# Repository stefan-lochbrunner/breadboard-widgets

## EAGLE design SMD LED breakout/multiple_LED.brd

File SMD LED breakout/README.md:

# SMD LED breakout
------------------

Straight forward SMD LED breakout. To be used between the inside of a breadboard and its power rails. [more info](https://hackaday.io/project/6332-breadboard-widgets/log/27568-1-5x-smd-led-breakout)

#### Single

#### Multi

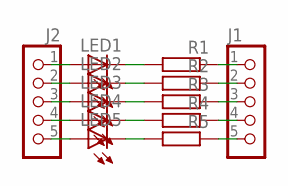
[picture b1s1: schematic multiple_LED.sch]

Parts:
J1, J2: CON_HEADER_1X05-PTH; M1X5
LED1, LED2, LED3, LED4, LED5: LED-0805; LED-805
R1, R2, R3, R4, R5: RESISTOR-0603; R603

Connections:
IN: J2.1, LED1.A
IN1: J2.2, LED2.A
IN2: J2.3, LED3.A
IN3: J2.4, LED4.A
IN4: J2.5, LED5.A
unnamed: LED2.C, R2.2
unnamed: LED1.C, R1.2
unnamed: LED3.C, R3.2
unnamed: LED4.C, R4.2
unnamed: LED5.C, R5.2
OUT: J1.1, R1.1
OUT1: J1.2, R2.1
OUT2: J1.3, R3.1
OUT3: J1.4, R4.1
OUT4: J1.5, R5.1

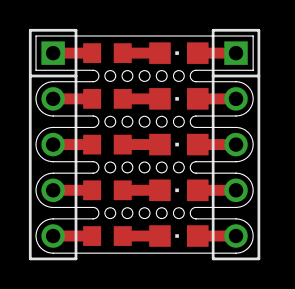
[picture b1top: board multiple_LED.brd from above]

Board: 2 copper layers, 12.1 x 12.1 mm, 12 parts (0 on the bottom side), 15 nets.

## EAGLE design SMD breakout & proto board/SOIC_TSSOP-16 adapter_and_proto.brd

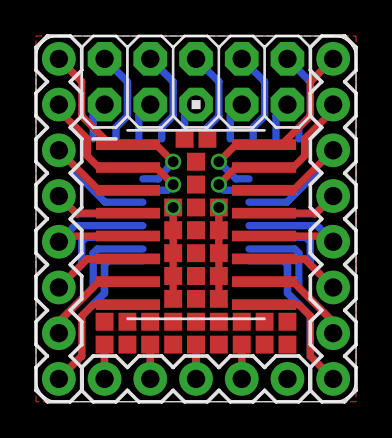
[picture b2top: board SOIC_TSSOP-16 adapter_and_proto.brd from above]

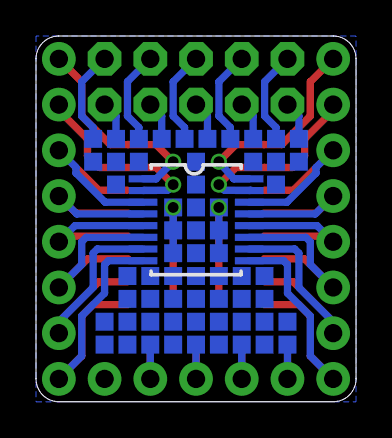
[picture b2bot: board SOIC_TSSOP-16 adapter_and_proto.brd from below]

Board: 2 copper layers, 17.8 x 20.3 mm, 104 parts (62 on the bottom side), 33 nets.

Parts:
JP1, JP2: 1X08_ROUND
JP3: AVR_ICSP
JP4: 1X05
SOIC-16: SOIC-16NW
TP1, TP2, TP3, TP4, TP5, TP6, TP7, TP8, TP9, TP10, TP11, TP12, TP13, TP14, TP15, TP16, TP17, TP18, TP19, TP20, TP21, TP22, TP23, TP24, TP25, TP26, TP27, TP28, TP29, TP30, TP31, TP32, TP33, TP34, TP35, TP36, TP37, TP38, TP39, TP40, TP41, TP42, TP43, TP44, TP45, TP46, TP47, TP48, TP49, TP50, TP51, TP52, TP53, TP54, TP55, TP56, TP57, TP58, TP59, TP60, TP61, TP62, TP63, TP64, TP65, TP66, TP67, TP68, TP69, TP70, TP71, TP72, TP73, TP74, TP75, TP76, TP77, TP78, TP79, TP80, TP81, TP82, TP83, TP84, TP85, TP86, TP87, TP88, TP89, TP90, TP91, TP92, TP93, TP94, TP95, TP96, TP97, TP98: TPSQTP10SQ; TP10SQ
TSSOP-16: TSSOP16

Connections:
1: JP1.8, SOIC-16.P1, TSSOP-16.16
2: JP1.7, SOIC-16.P2, TSSOP-16.15
3: JP1.6, SOIC-16.P3, TSSOP-16.14
4: JP1.5, SOIC-16.P4, TSSOP-16.13
5: JP1.4, SOIC-16.P5, TSSOP-16.12
6: JP1.3, SOIC-16.P6, TSSOP-16.11
7: JP1.2, SOIC-16.P7, TSSOP-16.10
8: JP1.1, SOIC-16.P8, TSSOP-16.9
9: JP2.8, SOIC-16.P9, TSSOP-16.8
10: JP2.7, SOIC-16.P10, TSSOP-16.7
11: JP2.6, SOIC-16.P11, TSSOP-16.6
12: JP2.5, SOIC-16.P12, TSSOP-16.5
13: JP2.4, SOIC-16.P13, TSSOP-16.4
14: JP2.3, SOIC-16.P14, TSSOP-16.3
15: JP2.2, SOIC-16.P15, TSSOP-16.2
16: JP2.1, SOIC-16.P16, TSSOP-16.1
D+: JP4.3, TP13.TP, TP17.TP
D-: JP4.2, TP14.TP, TP18.TP
GND: JP4.5, TP11.TP, TP20.TP
ID: JP4.4, TP12.TP, TP16.TP
unnamed: JP3.1, TP1.TP
unnamed: JP3.3, TP2.TP
unnamed: JP3.5, TP3.TP
unnamed: JP3.7, TP4.TP
unnamed: JP3.9, TP5.TP
unnamed: JP3.2, TP6.TP
unnamed: JP3.4, TP7.TP
unnamed: JP3.6, TP8.TP
unnamed: JP3.8, TP9.TP
unnamed: JP3.10, TP10.TP
RAIL1: TP25.TP, TP26.TP, TP27.TP, TP36.TP, TP37.TP, TP38.TP, TP39.TP, TP40.TP
RAIL2: TP28.TP, TP29.TP, TP30.TP, TP31.TP, TP32.TP, TP33.TP, TP34.TP, TP35.TP
VDD: JP4.1, TP15.TP, TP19.TP

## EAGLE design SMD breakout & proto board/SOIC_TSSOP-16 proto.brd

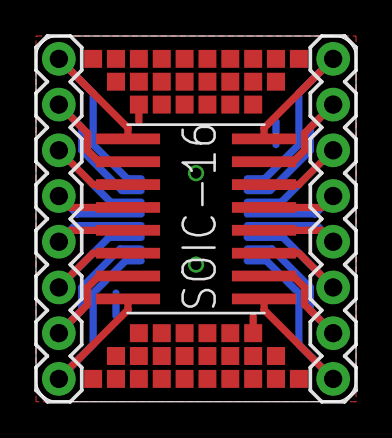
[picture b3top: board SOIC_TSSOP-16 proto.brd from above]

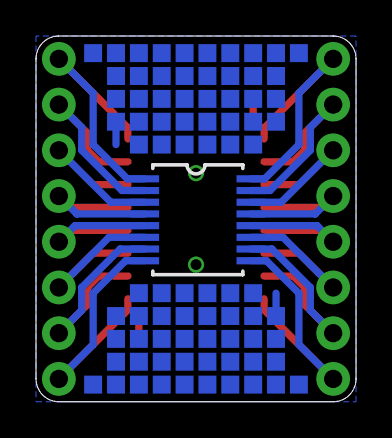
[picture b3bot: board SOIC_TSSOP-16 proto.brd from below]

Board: 2 copper layers, 17.8 x 20.3 mm, 132 parts (81 on the bottom side), 17 nets.

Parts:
E$1, E$2, E$3, E$4, E$5, E$6, E$7, E$8, E$9, E$10, E$11, E$12, E$13, E$14, E$15, E$16, E$17, E$18, E$19, E$20, E$21, E$22, E$23, E$24, E$25, E$26, E$27, E$28, E$29, E$30, E$31, E$32, E$33, E$34, E$35, E$36, E$37, E$38, E$39, E$40, E$41, E$42, E$43, E$44, E$45, E$46, E$47, E$48, E$49, E$50, E$51, E$52, E$53, E$54, E$55, E$56, E$57, E$58, E$59, E$60, E$61, E$62, E$63, E$64, E$65, E$66, E$67, E$68, E$69, E$70, E$71, E$72, E$73, E$74, E$75, E$76, E$77, E$78, E$79, E$80, E$81, E$82, E$83, E$84, E$85, E$86, E$87, E$88, E$89, E$90, E$91, E$92, E$93, E$94, E$95, E$96, E$97, E$98, E$99, E$100, E$101, E$102, E$103, E$104, E$105, E$106, E$107, E$108, E$109, E$110, E$111, E$112, E$113, E$114, E$115, E$116, E$117, E$118, E$119, E$120, E$121, E$122, E$124, E$125, E$126, E$127, E$128: TP10SQ
GND: TP10SQ
JP1, JP2: 1X08_ROUND
SOIC-16: SOIC-16; SOIC-16NW
U$2: TSSOP-16; TSSOP16

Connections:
1: JP1.8, SOIC-16.P1, U$2.16
2: JP1.7, SOIC-16.P2, U$2.15
3: JP1.6, SOIC-16.P3, U$2.14
4: JP1.5, SOIC-16.P4, U$2.13
5: JP1.4, SOIC-16.P5, U$2.12
6: JP1.3, SOIC-16.P6, U$2.11
7: JP1.2, SOIC-16.P7, U$2.10
8: JP1.1, SOIC-16.P8, U$2.9
9: JP2.8, SOIC-16.P9, U$2.8
10: JP2.7, SOIC-16.P10, U$2.7
11: JP2.6, SOIC-16.P11, U$2.6
12: JP2.5, SOIC-16.P12, U$2.5
13: JP2.4, SOIC-16.P13, U$2.4
14: JP2.3, SOIC-16.P14, U$2.3
15: JP2.2, SOIC-16.P15, U$2.2
16: JP2.1, SOIC-16.P16, U$2.1
GND: E$20.TP, E$30.TP, E$84.TP, GND.TP

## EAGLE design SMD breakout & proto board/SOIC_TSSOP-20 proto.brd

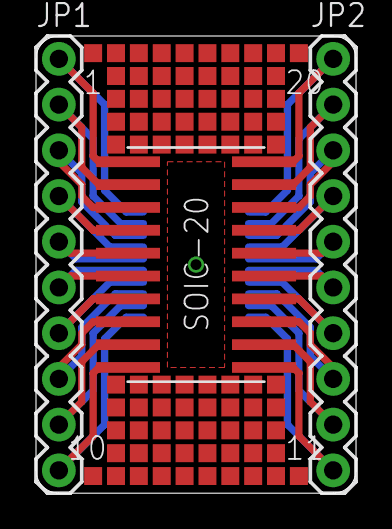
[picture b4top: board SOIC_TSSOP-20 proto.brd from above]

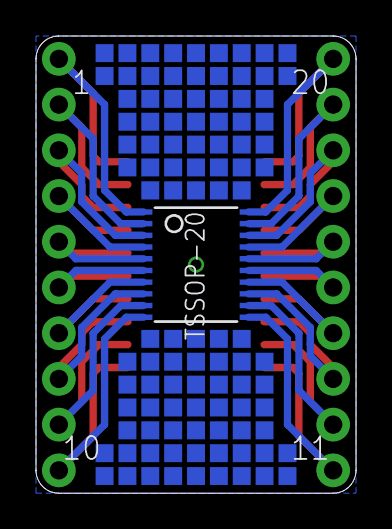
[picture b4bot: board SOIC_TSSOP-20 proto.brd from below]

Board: 2 copper layers, 17.8 x 25.4 mm, 190 parts (103 on the bottom side), 20 nets.

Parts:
E$1, E$2, E$3, E$4, E$5, E$6, E$7, E$8, E$9, E$10, E$11, E$12, E$13, E$14, E$15, E$16, E$17, E$18, E$19, E$20, E$21, E$22, E$23, E$24, E$25, E$26, E$27, E$28, E$29, E$30, E$31, E$32, E$33, E$34, E$35, E$36, E$37, E$38, E$39, E$40, E$41, E$42, E$43, E$44, E$45, E$46, E$47, E$48, E$49, E$50, E$51, E$52, E$53, E$54, E$55, E$56, E$57, E$58, E$59, E$60, E$61, E$62, E$63, E$64, E$65, E$66, E$67, E$68, E$69, E$70, E$71, E$72, E$73, E$74, E$75, E$76, E$77, E$78, E$79, E$80, E$81, E$82, E$83, E$84, E$85, E$86, E$87, E$88, E$89, E$90, E$91, E$92, E$93, E$94, E$95, E$96, E$97, E$98, E$99, E$100, E$101, E$102, E$103, E$104, E$105, E$106, E$107, E$108, E$109, E$110, E$111, E$112, E$113, E$114, E$115, E$116, E$117, E$118, E$119, E$120, E$121, E$122, E$123, E$124, E$125, E$126, E$127, E$128, E$129, E$130, E$131, E$132, E$133, E$134, E$135, E$136, E$137, E$138, E$139, E$140, E$141, E$142, E$143, E$144, E$145, E$146, E$147, E$148, E$149, E$150, E$151, E$152, E$153, E$154, E$155, E$156, E$157, E$158, E$159, E$160, E$161, E$162, E$163, E$164, E$165, E$166, E$167, E$168, E$169, E$170, E$171, E$172, E$173, E$174, E$175, E$176, E$177, E$178, E$179, E$180, E$181, E$182, E$183, E$184, E$185, E$186: TP10SQ
JP1, JP2: 1X10
SOIC-20: SOIC-20NW
TSSOP-20: TSSOP20

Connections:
1: JP1.10, SOIC-20.P1, TSSOP-20.20
2: JP1.9, SOIC-20.P2, TSSOP-20.19
3: JP1.8, SOIC-20.P3, TSSOP-20.18
4: JP1.7, SOIC-20.P4, TSSOP-20.17
5: JP1.6, SOIC-20.P5, TSSOP-20.16
6: JP1.5, SOIC-20.P6, TSSOP-20.15
7: JP1.4, SOIC-20.P7, TSSOP-20.14
8: JP1.3, SOIC-20.P8, TSSOP-20.13
9: JP1.2, SOIC-20.P9, TSSOP-20.12
10: JP1.1, SOIC-20.P10, TSSOP-20.11
11: JP2.1, SOIC-20.P11, TSSOP-20.10
12: JP2.2, SOIC-20.P12, TSSOP-20.9
13: JP2.3, SOIC-20.P13, TSSOP-20.8
14: JP2.4, SOIC-20.P14, TSSOP-20.7
15: JP2.5, SOIC-20.P15, TSSOP-20.6
16: JP2.6, SOIC-20.P16, TSSOP-20.5
17: JP2.7, SOIC-20.P17, TSSOP-20.4
18: JP2.8, SOIC-20.P18, TSSOP-20.3
19: JP2.9, SOIC-20.P19, TSSOP-20.2
20: JP2.10, SOIC-20.P20, TSSOP-20.1

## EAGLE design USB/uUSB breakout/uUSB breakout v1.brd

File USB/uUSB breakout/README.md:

# uUSB breakout
---------------

Main functionality is to provide "VUSB circuitry" for AVR microcontrollers. Can also be used as generic uUSB breakout by shorting 68R resistor footprints or as breadboard power supply (supplying 5V).
[**more info**](https://hackaday.io/project/6332-breadboard-widgets/log/19615-uusb-breakout)

#### v1

#### v2
~~Allows for supplying different voltages by populating the bottom side with desired regulator. For 5V short solder jumper.~~
Superseded by v3

#### v3
Allows for supplying different voltages by populating the bottom side with desired regulator. The following modes are possible:
- Supply rail and Vcc pin with 5V directly from USB (regulator not populated, short all 3 pads of solder jumper)
- Supply regulator with 5V from USB which in turn supplies rail and Vcc pin (short center and top pad)
- Supply regulator from rail and get regulated voltage on Vcc pin (short center and bottom pad)

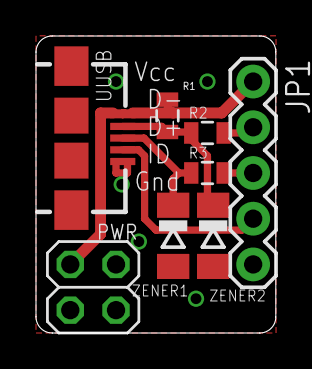
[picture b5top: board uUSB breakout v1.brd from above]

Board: 2 copper layers, 13.3 x 16.5 mm, 8 parts (0 on the bottom side), 7 nets.

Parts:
JP1: 1X05
PWR: 2X02
R1: 1.5k; 0805
R2, R3: 68; 0805
UUSB: USB-AB-MICRO-SMD
ZENER1, ZENER2: 3.6V; SOD80C

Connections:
D-: R1.1, R2.1, UUSB.D-, ZENER2.C
GND: JP1.5, PWR.4, UUSB.GND, ZENER1.A, ZENER2.A
ID: JP1.4, UUSB.ID
unnamed: JP1.2, R2.2
unnamed: JP1.3, R3.2
unnamed: R3.1, UUSB.D+, ZENER1.C
VCC: JP1.1, PWR.1, R1.2, UUSB.VBUS

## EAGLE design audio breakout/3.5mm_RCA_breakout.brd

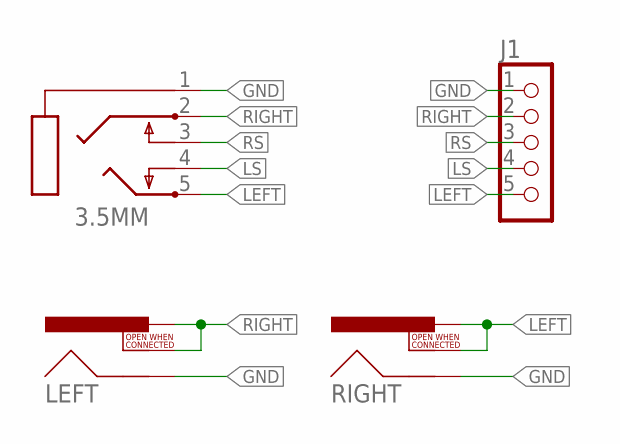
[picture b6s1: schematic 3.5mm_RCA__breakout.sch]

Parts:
3.5MM: STEREOJACK; STX3100
J1: CON_HEADER_1X05-PTH; M1X5
LEFT: RCA
RIGHT: RCA

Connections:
GND: 3.5MM.1, J1.1, LEFT.SHELL, RIGHT.SHELL
LEFT: 3.5MM.5, J1.5, RIGHT.PIN, RIGHT.SWITCH
LS: 3.5MM.4, J1.4
RIGHT: 3.5MM.2, J1.2, LEFT.PIN, LEFT.SWITCH
RS: 3.5MM.3, J1.3

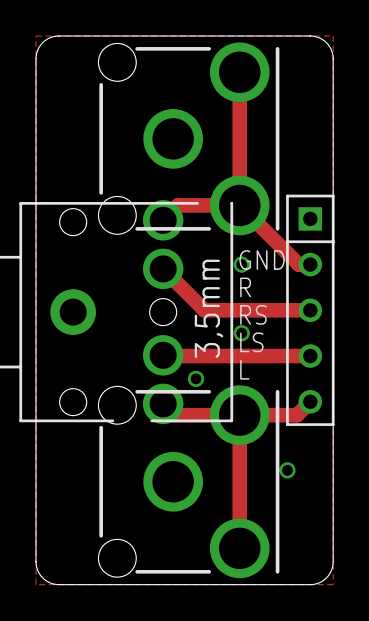
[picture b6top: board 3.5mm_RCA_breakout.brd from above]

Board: 2 copper layers, 16.5 x 30.5 mm, 4 parts (0 on the bottom side), 5 nets.

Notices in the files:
parts and their libraries:
Kevin-GenericICFootprints: Licensing: Creative Commons ShareAlike 4.0 International - https://creativecommons.org/licenses/by-sa/4.0
